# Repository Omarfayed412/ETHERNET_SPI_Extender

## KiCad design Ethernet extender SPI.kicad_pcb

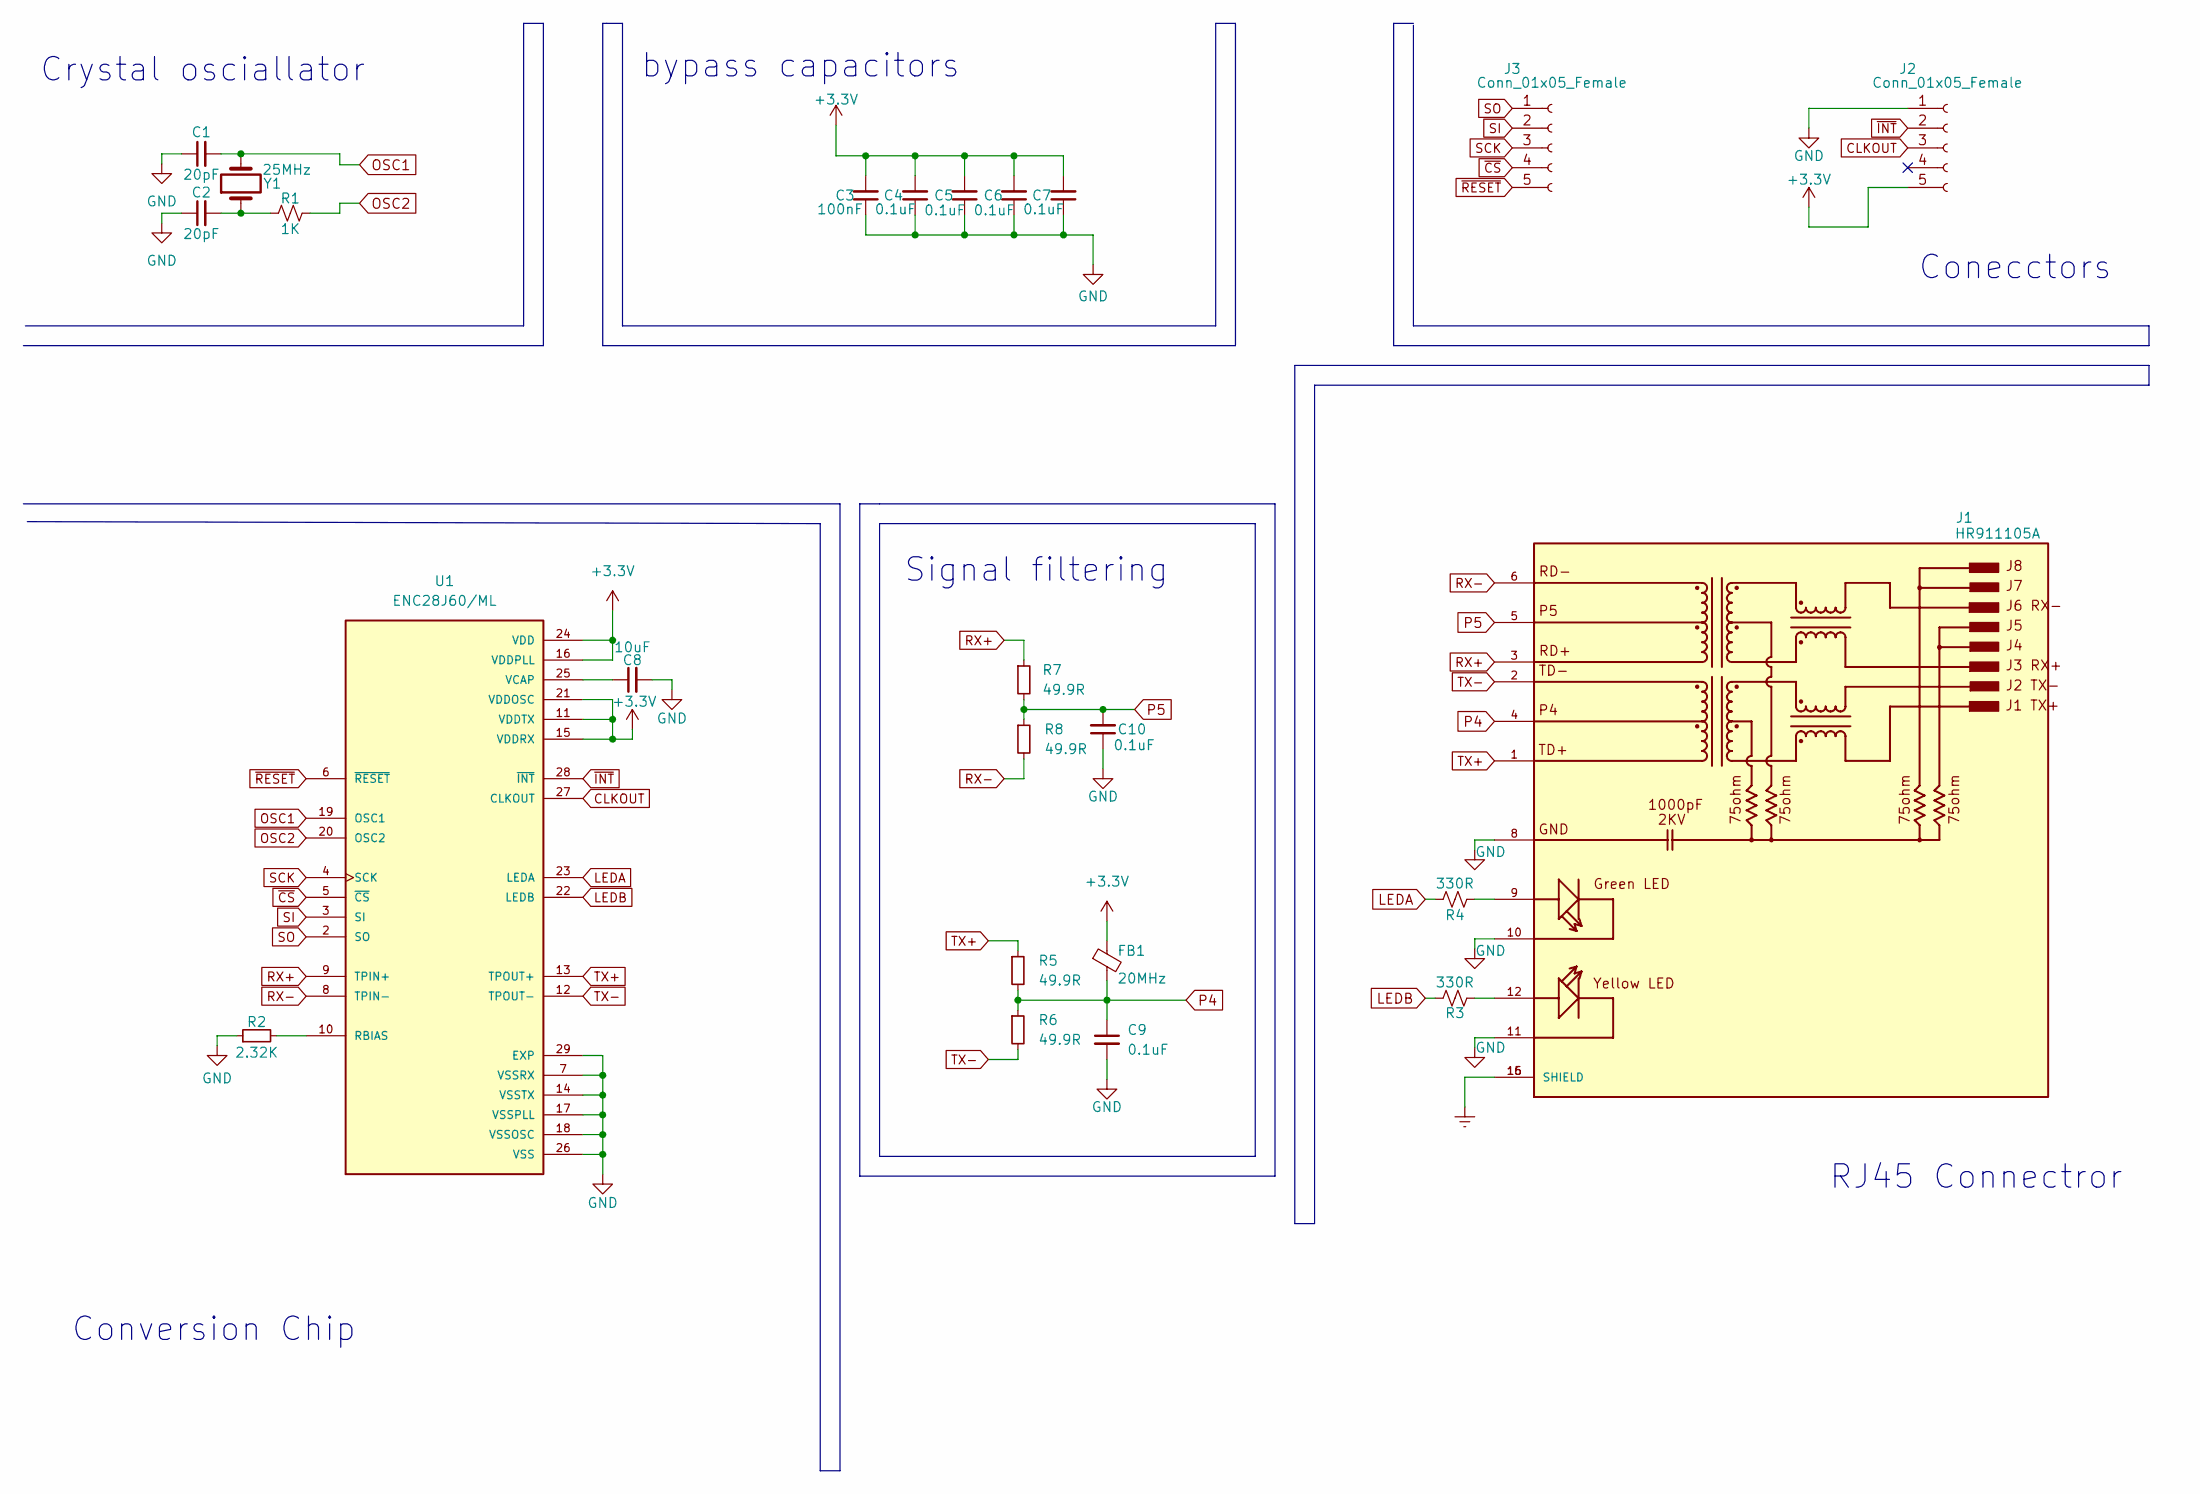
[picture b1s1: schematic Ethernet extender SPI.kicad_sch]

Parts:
C1, C2: 20pF; C_0402_1005Metric
C3: 100nF; C_0402_1005Metric
C4, C5, C6, C7, C9, C10: 0.1uF; C_0402_1005Metric
C8: 10uF; C_0603_1608Metric
FB1: 20MHz; L_0603_1608Metric
J1: HR911105A; HANRUN_HR911105A; PARTREV A
J2, J3: Conn_01x05_Female; PinSocket_1x05_P1.27mm_Vertical
R1: 1K; R_0603_1608Metric
R2: 2.32K; R_0603_1608Metric
R3, R4: 330R; R_0603_1608Metric
R5, R6, R7, R8: 49.9R; R_0603_1608Metric
U1: ENC28J60/ML; QFN65P600X600X100-29N; PARTREV E
Y1: 25MHz; Crystal_SMD_0603-2Pin_6.0x3.5mm_HandSoldering

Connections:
+3.3V: C3.2, C4.2, C5.2, C6.2, C7.2, FB1.1, J2.5, U1.11 (VDDTX), U1.15 (VDDRX), U1.16 (VDDPLL), U1.21 (VDDOSC), U1.24 (VDD)
CLKOUT: J2.3, U1.27 (CLKOUT)
Earth: J1.15 (SHIELD), J1.16 (SHIELD)
GND: C1.1, C2.1, C3.1, C4.1, C5.1, C6.1, C7.1, C8.2, C9.2, C10.1, J1.8, J1.10, J1.11, J2.1, R2.1, U1.7 (VSSRX), U1.14 (VSSTX), U1.17 (VSSPLL), U1.18 (VSSOSC), U1.26 (VSS), U1.29 (EXP)
LEDA: R4.2, U1.23 (LEDA)
LEDB: R3.2, U1.22 (LEDB)
unnamed: C2.2, R1.1, Y1.1
unnamed: C8.1, U1.25 (VCAP)
unnamed: J1.9, R4.1
unnamed: J1.12, R3.1
unnamed: R2.2, U1.10 (RBIAS)
OSC1: C1.2, U1.19 (OSC1), Y1.2
OSC2: R1.2, U1.20 (OSC2)
P4: C9.1, FB1.2, J1.4, R5.2, R6.1
P5: C10.2, J1.5, R7.2, R8.1
RX+: J1.3, R7.1, U1.9 (TPIN+)
RX-: J1.6, R8.2, U1.8 (TPIN-)
SCK: J3.3, U1.4 (SCK)
SI: J3.2, U1.3 (SI)
SO: J3.1, U1.2 (SO)
TX+: J1.1, R5.1, U1.13 (TPOUT+)
TX-: J1.2, R6.2, U1.12 (TPOUT-)
~CS: J3.4, U1.5 (~CS)
~INT: J2.2, U1.28 (~INT)
~RESET: J3.5, U1.6 (~RESET)

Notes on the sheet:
Conecctors
Conversion Chip
bypass capacitors
Crystal osciallator
Signal filtering
RJ45 Connectror

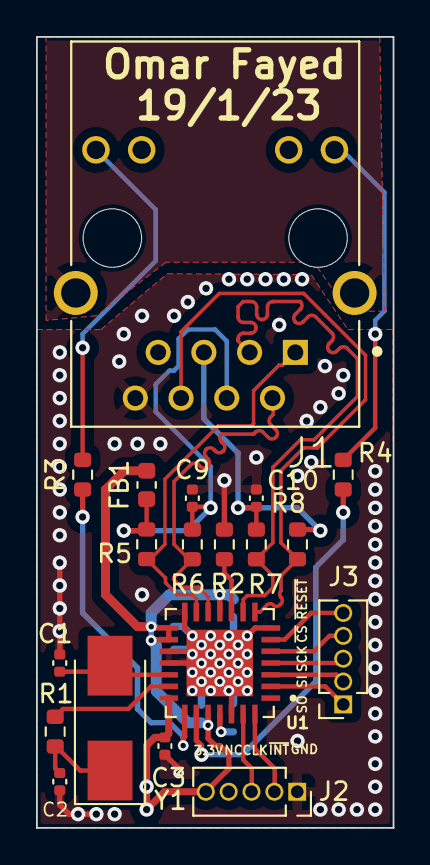
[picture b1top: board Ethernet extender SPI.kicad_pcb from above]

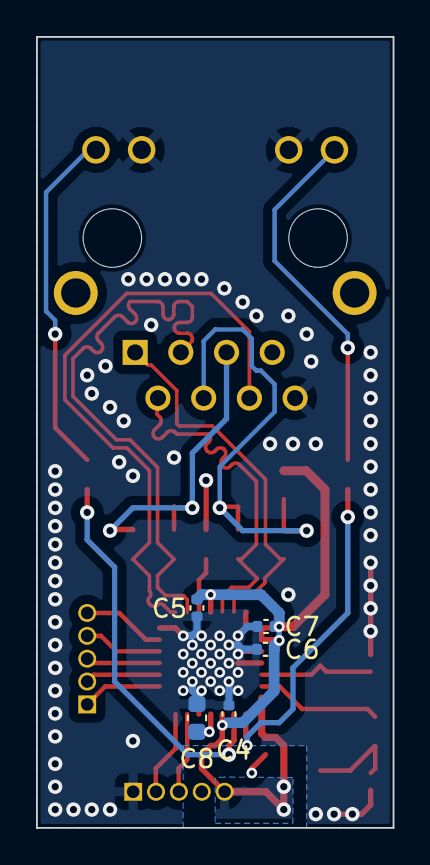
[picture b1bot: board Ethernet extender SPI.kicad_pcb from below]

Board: 4 copper layers, 19.8 x 43.9 mm, 24 parts (5 on the bottom side), 25 nets.

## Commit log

2023-11-23 Added all the design files for PCB for Kicad
